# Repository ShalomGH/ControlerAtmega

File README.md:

<h1>Universal controller with Atmega8</h1>
<ul>
    <li>3 outputs 220V</li>
    <li>3 inputs for buttons with RC-</li>
    <li>1 PWM output</li>
    <li>Power supply 220v-5v</li>
</ul>

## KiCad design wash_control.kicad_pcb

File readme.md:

<h1>Universal controller with Atmega8</h1>
<ul>
    <li>3 outputs 220V</li>
    <li>3 inputs for buttons with RC-</li>
    <li>1 PWM output</li>
    <li>Power supply 220v-5v</li>
</ul>

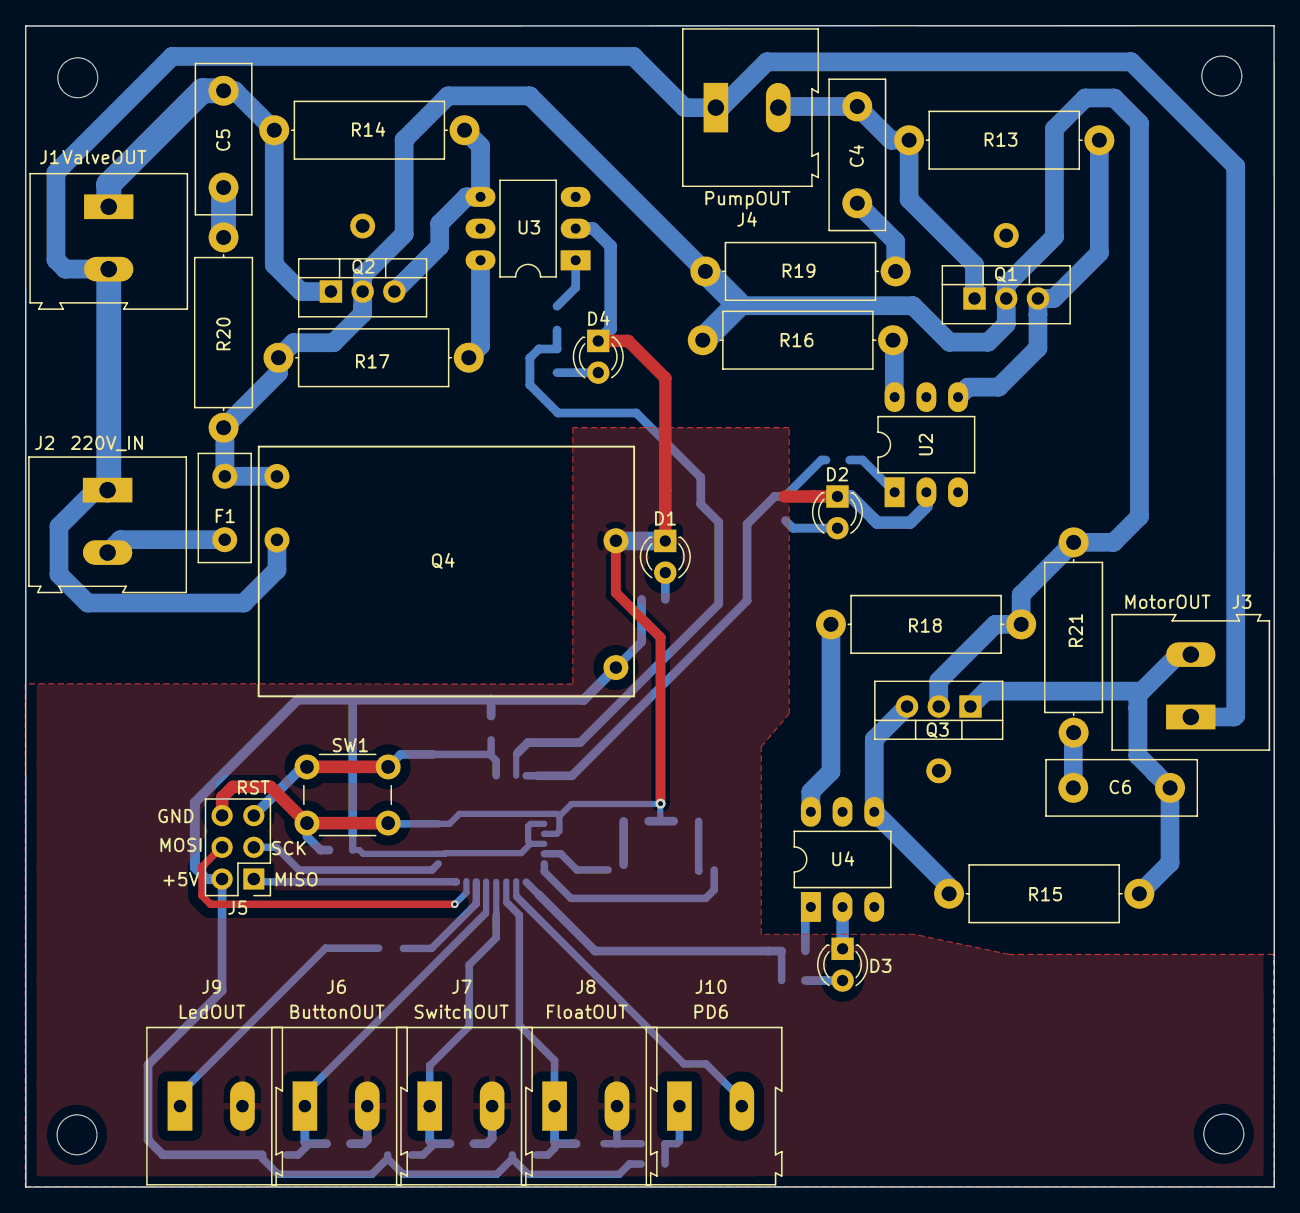
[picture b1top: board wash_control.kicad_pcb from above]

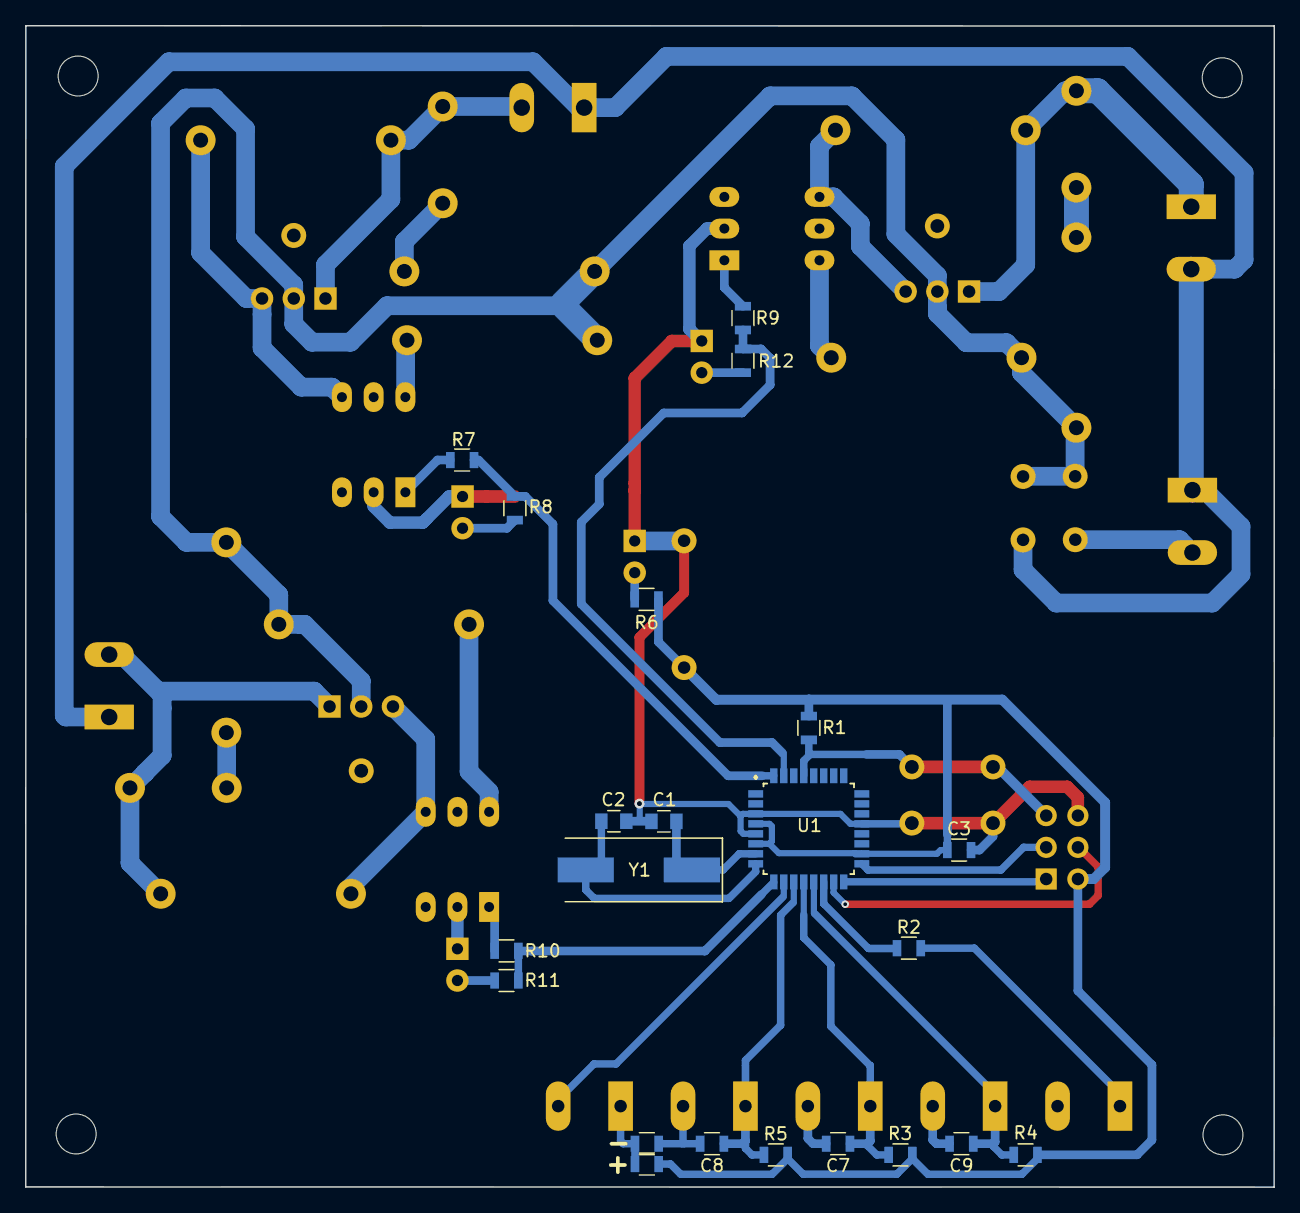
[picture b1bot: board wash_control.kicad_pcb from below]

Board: 2 copper layers, 100.0 x 93.0 mm, 57 parts (22 on the bottom side), 40 nets.

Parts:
C1, C2: 22p; C_0805
C3: 100nF; R_0805
C4, C5, C6: 0.01uF; C_Disc_D12.0mm_W4.4mm_P7.75mm
C7, C8, C9: 0.33uF; R_0805
D1, D2, D3, D4: LED; LED_D3.0mm
F1: Fuse; Fuse_TE5_Littlefuse-395Series
J1: ValveOUT; TerminalBlock_Altech_AK300-2_P5.00mm
J2: 220V_IN; TerminalBlock_Altech_AK300-2_P5.00mm
J3: MotorOUT; TerminalBlock_Altech_AK300-2_P5.00mm
J4: PumpOUT; TerminalBlock_Altech_AK300-2_P5.00mm
J5: ISCP; Pin_Header_Straight_2x03_Pitch2.54mm
J6: ButtonOUT; TerminalBlock_Altech_AK300-2_P5.00mm
J7: SwitchOUT; TerminalBlock_Altech_AK300-2_P5.00mm
J8: FloatOUT; TerminalBlock_Altech_AK300-2_P5.00mm
J9: LedOUT; TerminalBlock_Altech_AK300-2_P5.00mm
J10: PD6; TerminalBlock_Altech_AK300-2_P5.00mm
Q1, Q2, Q3: BT136; TO-220-3_Vertical
Q4: BP_12V; BP pod vpaiky
R1: 10k; R_0805
R2, R6: 270; R_0805
R3, R4, R5: 150k; R_0805
R7, R8, R9, R10, R11, R12: 220; R_0805
R13, R14, R15: 330; R_Axial_DIN0414_L11.9mm_D4.5mm_P15.24mm_Horizontal
R16, R17, R18: 390; R_Axial_DIN0414_L11.9mm_D4.5mm_P15.24mm_Horizontal
R19, R20, R21: 39; R_Axial_DIN0414_L11.9mm_D4.5mm_P15.24mm_Horizontal
R22, R23: R; R_0805
SW1: SW_Push; SW_PUSH_6mm
U1: ATmega8A-AU; LQFP-32_7x7mm_Pitch0.8mm
U2, U3, U4: MOC3023M; DIP-6_W7.62mm_LongPads
Y1: 16MHz; Crystal_SMD_HC49-SD

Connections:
+5V: C3.2, J5.2, Q4.3, R1.1, R3.1, R4.1, R5.1, R6.1, R22.2, U1.4, U1.6, U1.18
/220_In1: F1.2, Q1.2, Q2.2, Q3.2, Q4.1, R16.1, R17.1, R18.1, R19.2, R20.2, R21.2
/220_In2: J1.2, J2.1, J3.1, J4.1, Q4.2
/Button: C9.1, J6.1, R4.2, U1.13
/Float: C8.1, J8.1, R5.2, U1.11
/Led: J9.1, R2.1
/MISO: J5.1, U1.16
/MOSI: J5.4, U1.15
/Motor: C6.1, J3.2, Q3.1, R15.1
/MotorPin: R10.2, R11.2, U1.9
/PD6: J10.2, U1.10
/Pump: C4.1, J4.2, Q1.1, R13.1
/PumpPin: R7.2, R8.2, U1.32
/RST: J5.5, R1.2, SW1.2, U1.29
/SCK: J5.3, U1.17
/Switch: C7.1, J7.1, R3.2, U1.12
/Valve: C5.1, J1.1, Q2.1, R14.1
/ValvePin: R9.2, R12.2, U1.31
Earth: C1.2, C2.2, C3.1, C7.2, C8.2, C9.2, D1.1, D2.1, D3.1, D4.1, J5.6, J6.2, J7.2, J8.2, J9.2, Q4.4, R23.2, SW1.1, U1.3, U1.5, U1.21, U2.2, U3.2, U4.2
unnamed: C1.1, U1.7, Y1.1
unnamed: C2.1, U1.8, Y1.2
unnamed: C4.2, R19.1
unnamed: C5.2, R20.1
unnamed: C6.2, R21.1
unnamed: D1.2, R6.2
unnamed: D2.2, R8.1
unnamed: D3.2, R11.1
unnamed: D4.2, R12.1
unnamed: F1.1, J2.2
unnamed: J10.1, R22.1, R23.1
unnamed: Q1.3, R13.2, U2.4
unnamed: Q2.3, R14.2, U3.4
unnamed: Q3.3, R15.2, U4.4
unnamed: R2.2, U1.14
unnamed: R7.1, U2.1
unnamed: R9.1, U3.1
unnamed: R10.1, U4.1
unnamed: R16.2, U2.6
unnamed: R17.2, U3.6
unnamed: R18.2, U4.6

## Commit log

2019-12-04 Схема готова
2019-12-04 + net
2019-12-05 Все посадочные
2019-12-06 + PCB
2019-12-13 5.0
    Плата готова
2021-08-14 Remake all project
2021-08-14 Rename readme.md to README.md
2021-08-15 merge
